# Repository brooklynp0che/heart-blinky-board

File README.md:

# heart-blinky-board

originally designed to be a sun ( hence the name sunny ) but changed to be a heart 555 blinky board :) my first pcb design !!

made for the STASIS hackathon, run by hackclub !!

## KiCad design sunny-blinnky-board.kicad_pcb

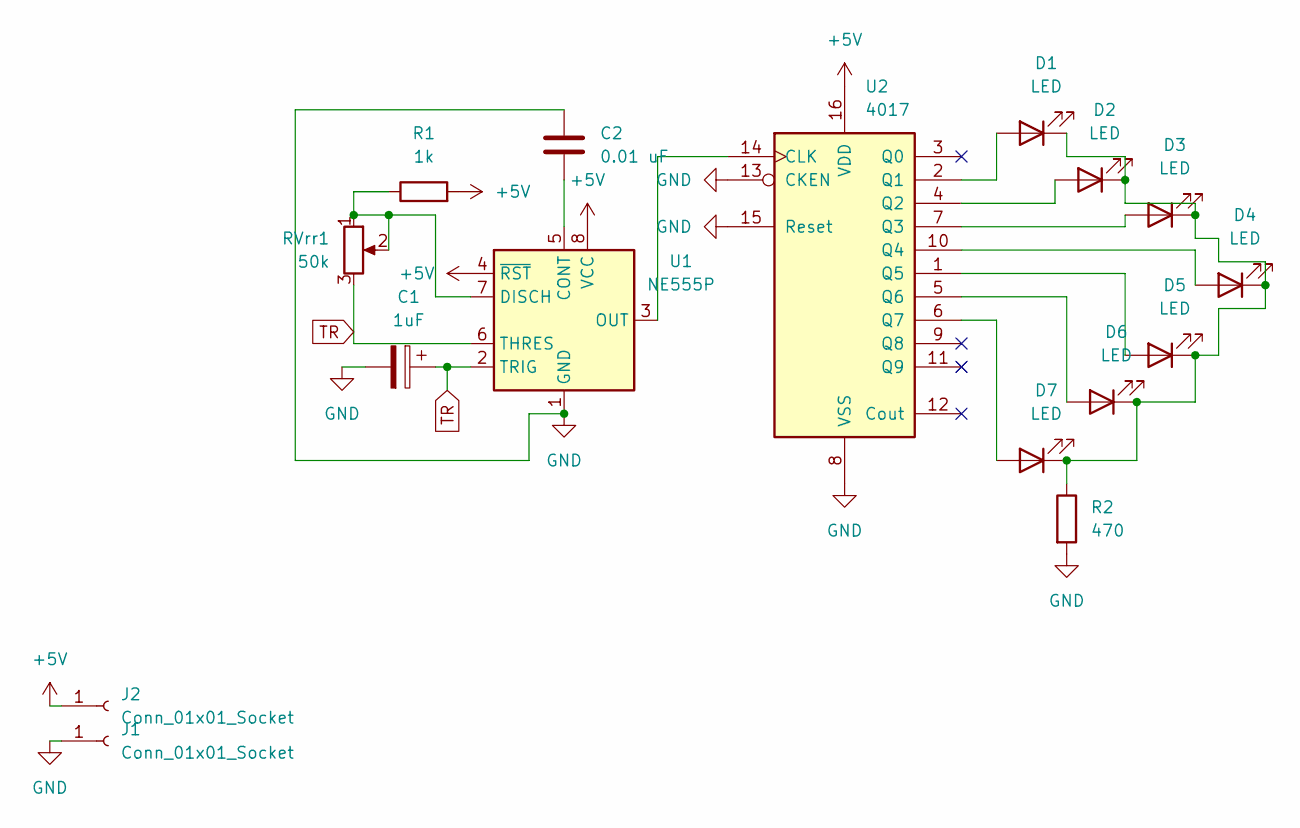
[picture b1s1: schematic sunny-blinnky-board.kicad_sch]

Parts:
C1: 1uF; CP_Radial_D5.0mm_P2.00mm
C2: 0.01 uF; C_Disc_D7.5mm_W2.5mm_P5.00mm
D1, D2, D3, D4, D5, D6, D7: LED; LED_D3.0mm
J1, J2: Conn_01x01_Socket; PinHeader_1x02_P2.54mm_Vertical
R1: 1k; R_Axial_DIN0207_L6.3mm_D2.5mm_P7.62mm_Horizontal
R2: 470; R_Axial_DIN0207_L6.3mm_D2.5mm_P7.62mm_Horizontal
RVrr1: 50k; Potentiometer_Vishay_T93YA_Vertical
U1: NE555P; DIP-8_W7.62mm
U2: 4017; N16

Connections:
+5V: J2.1, R1.2, U1.4 (~RST), U1.8 (VCC), U2.16 (VDD)
GND: C1.2, C2.1, J1.1, R2.2, U1.1 (GND), U2.8 (VSS), U2.13 (CKEN), U2.15 (Reset)
unnamed: D1.2 (A), U2.2 (Q1)
unnamed: D1.1 (K), D2.1 (K), D3.1 (K), D4.1 (K), D5.1 (K), D6.1 (K), D7.1 (K), R2.1
unnamed: D2.2 (A), U2.4 (Q2)
unnamed: D3.2 (A), U2.7 (Q3)
unnamed: D4.2 (A), U2.10 (Q4)
unnamed: D5.2 (A), U2.1 (Q5)
unnamed: D6.2 (A), U2.5 (Q6)
unnamed: D7.2 (A), U2.6 (Q7)
unnamed: C2.2, U1.5 (CONT)
unnamed: R1.1, RVrr1.1, RVrr1.2, U1.7 (DISCH)
unnamed: U1.3 (OUT), U2.14 (CLK)
TR: C1.1, RVrr1.3, U1.2 (TRIG), U1.6 (THRES)

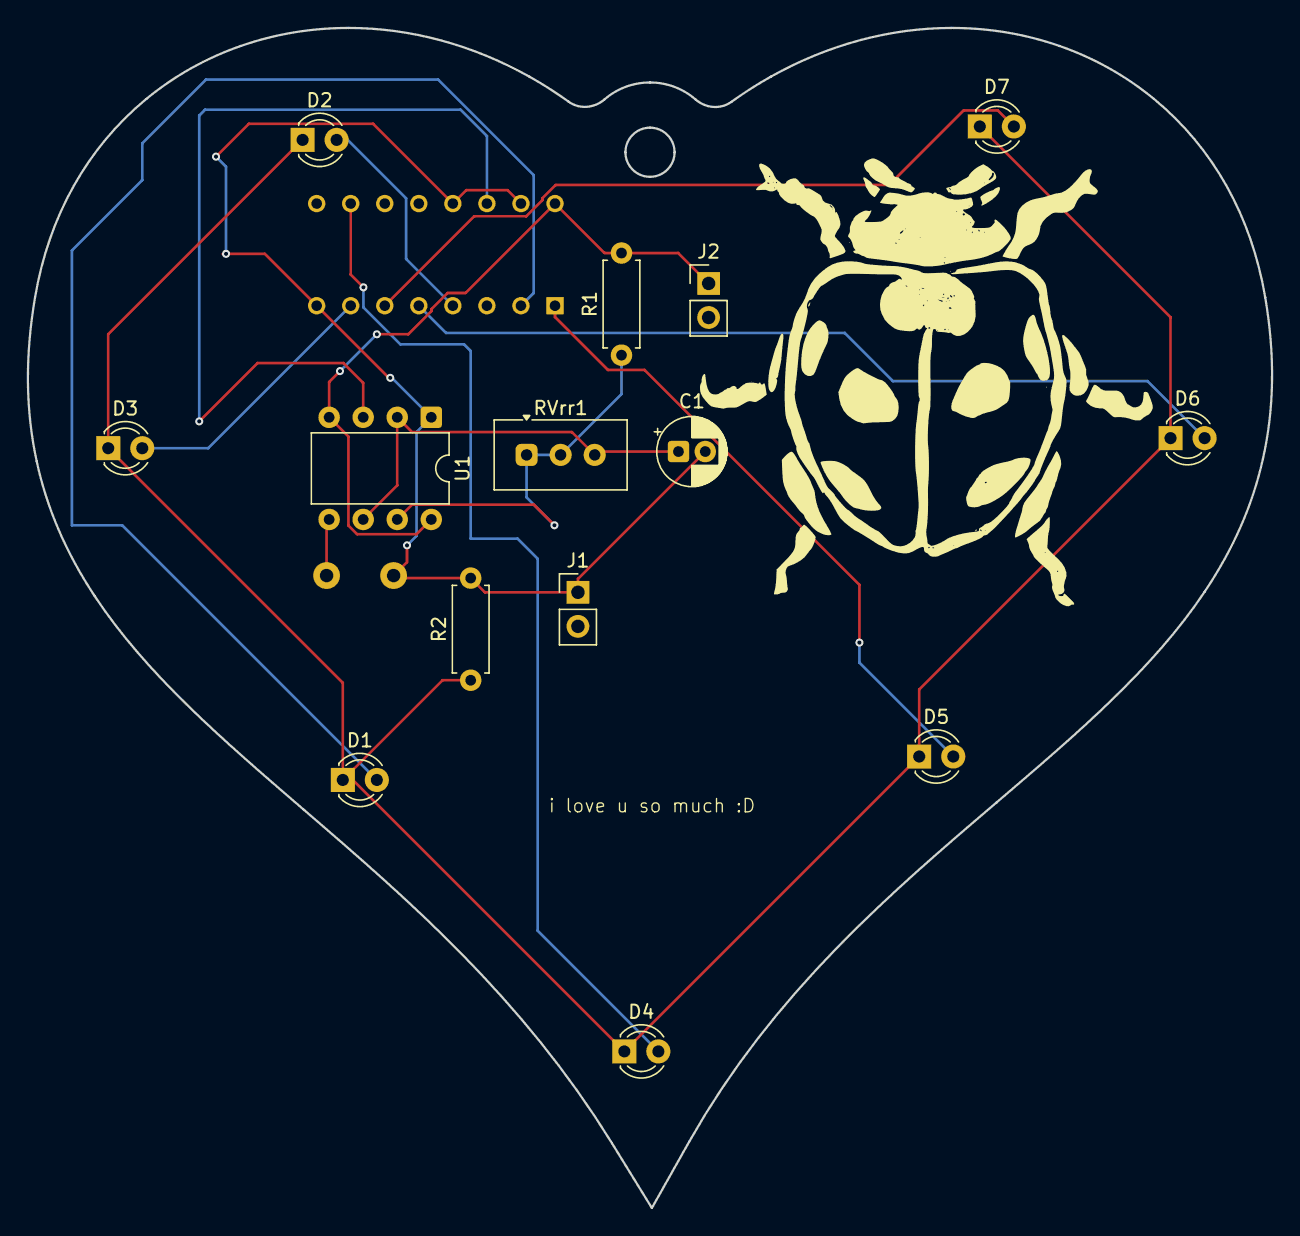
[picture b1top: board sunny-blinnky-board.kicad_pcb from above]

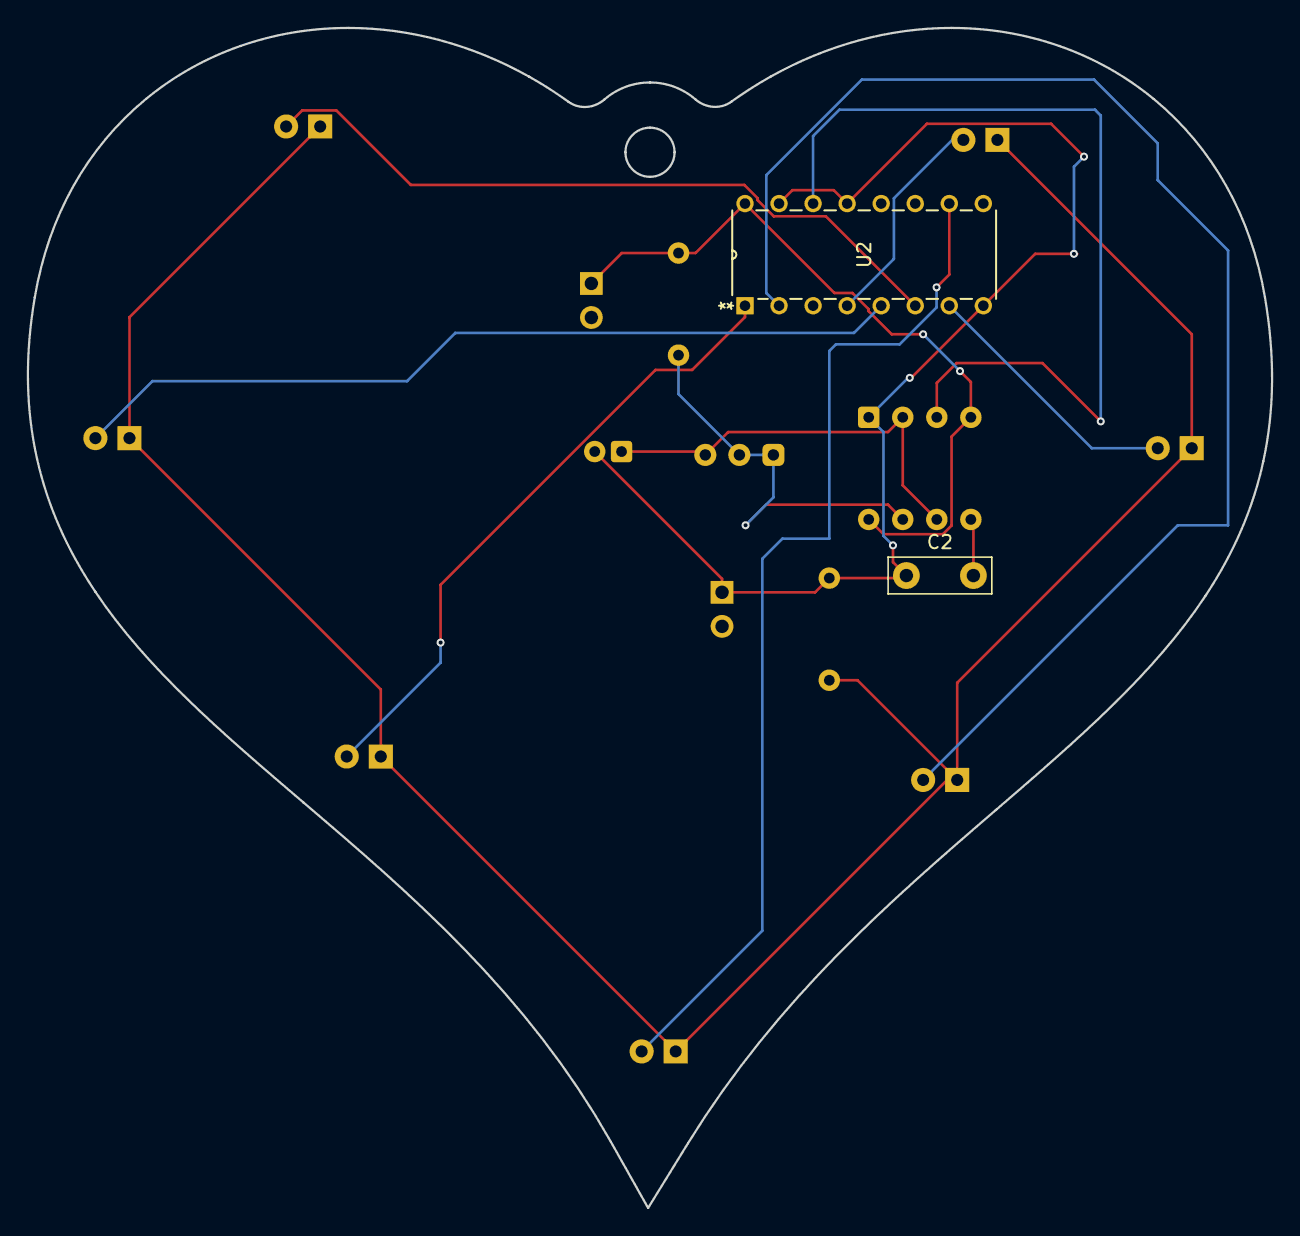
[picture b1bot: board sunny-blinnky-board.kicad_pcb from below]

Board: 2 copper layers, 92.8 x 88.0 mm, 16 parts (2 on the bottom side), 14 nets.

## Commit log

2026-04-02 Enhance README with project details and image
    Added additional context and image to README.
